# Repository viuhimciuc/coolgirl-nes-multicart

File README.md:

# 🎮 COOLGIRL - Ultimate Multigame Cartridge for Nintendo Entertainment System

The goal of this project is to create a Nintendo Entertainment System (NES) cartridge in KiCad based on the [coolgirl-famicom-multicart](https://github.com/ClusterM/coolgirl-famicom-multicart) project. This hardware design remains functionally identical to ClusterM's original project and can support up to ~700 games across various mappers.

### 🛠️ Architecture Overview
* **🧠 CPLD Core**: Uses the EPM1270T144 chip to emulate various mappers.
* **💾 Memory Layout**: PRG and CHR data share a single flash memory chip.
* **⚡ Boot Sequence**: The bootloader copies CHR data from Flash to CHR-RAM before game launch.
* **⚙️ Configuration**: Registers manage PRG offsets, bank modes, and mapper IDs.
* **🔒 Security**: Features a dedicated write-protection lock bit to secure settings after configuration.

## 📋 Full Characteristics
* **PRG ROM**: Up to 128 MiB
* **CHR RAM**: Up to 512 KiB
* **PRG RAM**: 32 KiB, non-volatile (FRAM) (optional)

---

## 🚀 How to Build

### 🔌 Hardware

#### 📄 Bill of Materials
* 🛒 [BoM](Coolgirl-NES_Rev6.x/production/bom.csv)

#### 🗺️ Schematic

* The [kicad_sch](Coolgirl-NES_Rev6.x/Coolgirl-NES_Rev6.x.kicad_sch) file can be opened using [KiCad](https://kicad.org).
 
#### 🎛️ PCB Design
The board is designed for ordering on [jlcpcb.com](https://jlcpcb.com).

| 🟢 3D Render (Top) | 🔵 3D Render (Bottom) |
| :---: | :---: |
|  |  |

* **Layers**: 2
* **PCB Thickness**: 1.2mm
* **Edge Connectors**: Gold fingers are highly recommended

* 📂 Layout source: [kicad_pcb](Coolgirl-NES_Rev6.x/Coolgirl-NES_Rev6.x.kicad_pcb) can be opened using [KiCad](https://kicad.org).
* 📦 Production files: Generated gerbers are located in the [Coolgirl-NES_Rev6.x/production](Coolgirl-NES_Rev6.x/production) directory.

### 💾 Firmware
All firmware and register descriptions are sourced from the [coolgirl-famicom-multicart](https://github.com/ClusterM/coolgirl-famicom-multicart/tree/master) project, corresponding to the board revision.

EPM1270T144 CPLD firmware can be compiled using the [Quartus Prime Lite 21.1](https://www.altera.com/downloads/fpga-development-tools/quartus-prime-lite-edition-design-software-version-21-1-windows). Open [CoolGirl.qpf](https://github.com/ClusterM/coolgirl-famicom-multicart/blob/master/CoolGirl_rev6.x/CoolGirl.qpf) to configure and compile project.

All mappers can't fit into the CPLD at once, so you need to select required mappers in [config file](https://github.com/ClusterM/coolgirl-famicom-multicart/blob/master/CoolGirl_config.vh), so they can fit into 1270 macrocells. Also, you can set `RESET_COMBINATION` parameter to specify software reset button combination, it works on original consoles and some famiclones. Default combination is `8'b11010010` (Left+Start+A+B). Set it to 0 to disable and free some macrocells.

There are JTAG pads on the cartridge board to connect programmer (USB Blaster).

### 💿 ROM Preparing
You can use my [COOLGIRL Multirom Builder based on ca65](https://github.com/viuhimciuc/coolgirl-multirom-builder-ca65)

and also use from [COOLGIRL Multirom Builder](https://github.com/ClusterM/coolgirl-multirom-builder)

to combine multiple ROMs into one with menu and loader. ROM can be written to assembled cartridge using [Famicom/NES Dumper/Writer](https://github.com/ClusterM/famicom-dumper-writer). Non-soldered flash memory chip can be written using programmer.

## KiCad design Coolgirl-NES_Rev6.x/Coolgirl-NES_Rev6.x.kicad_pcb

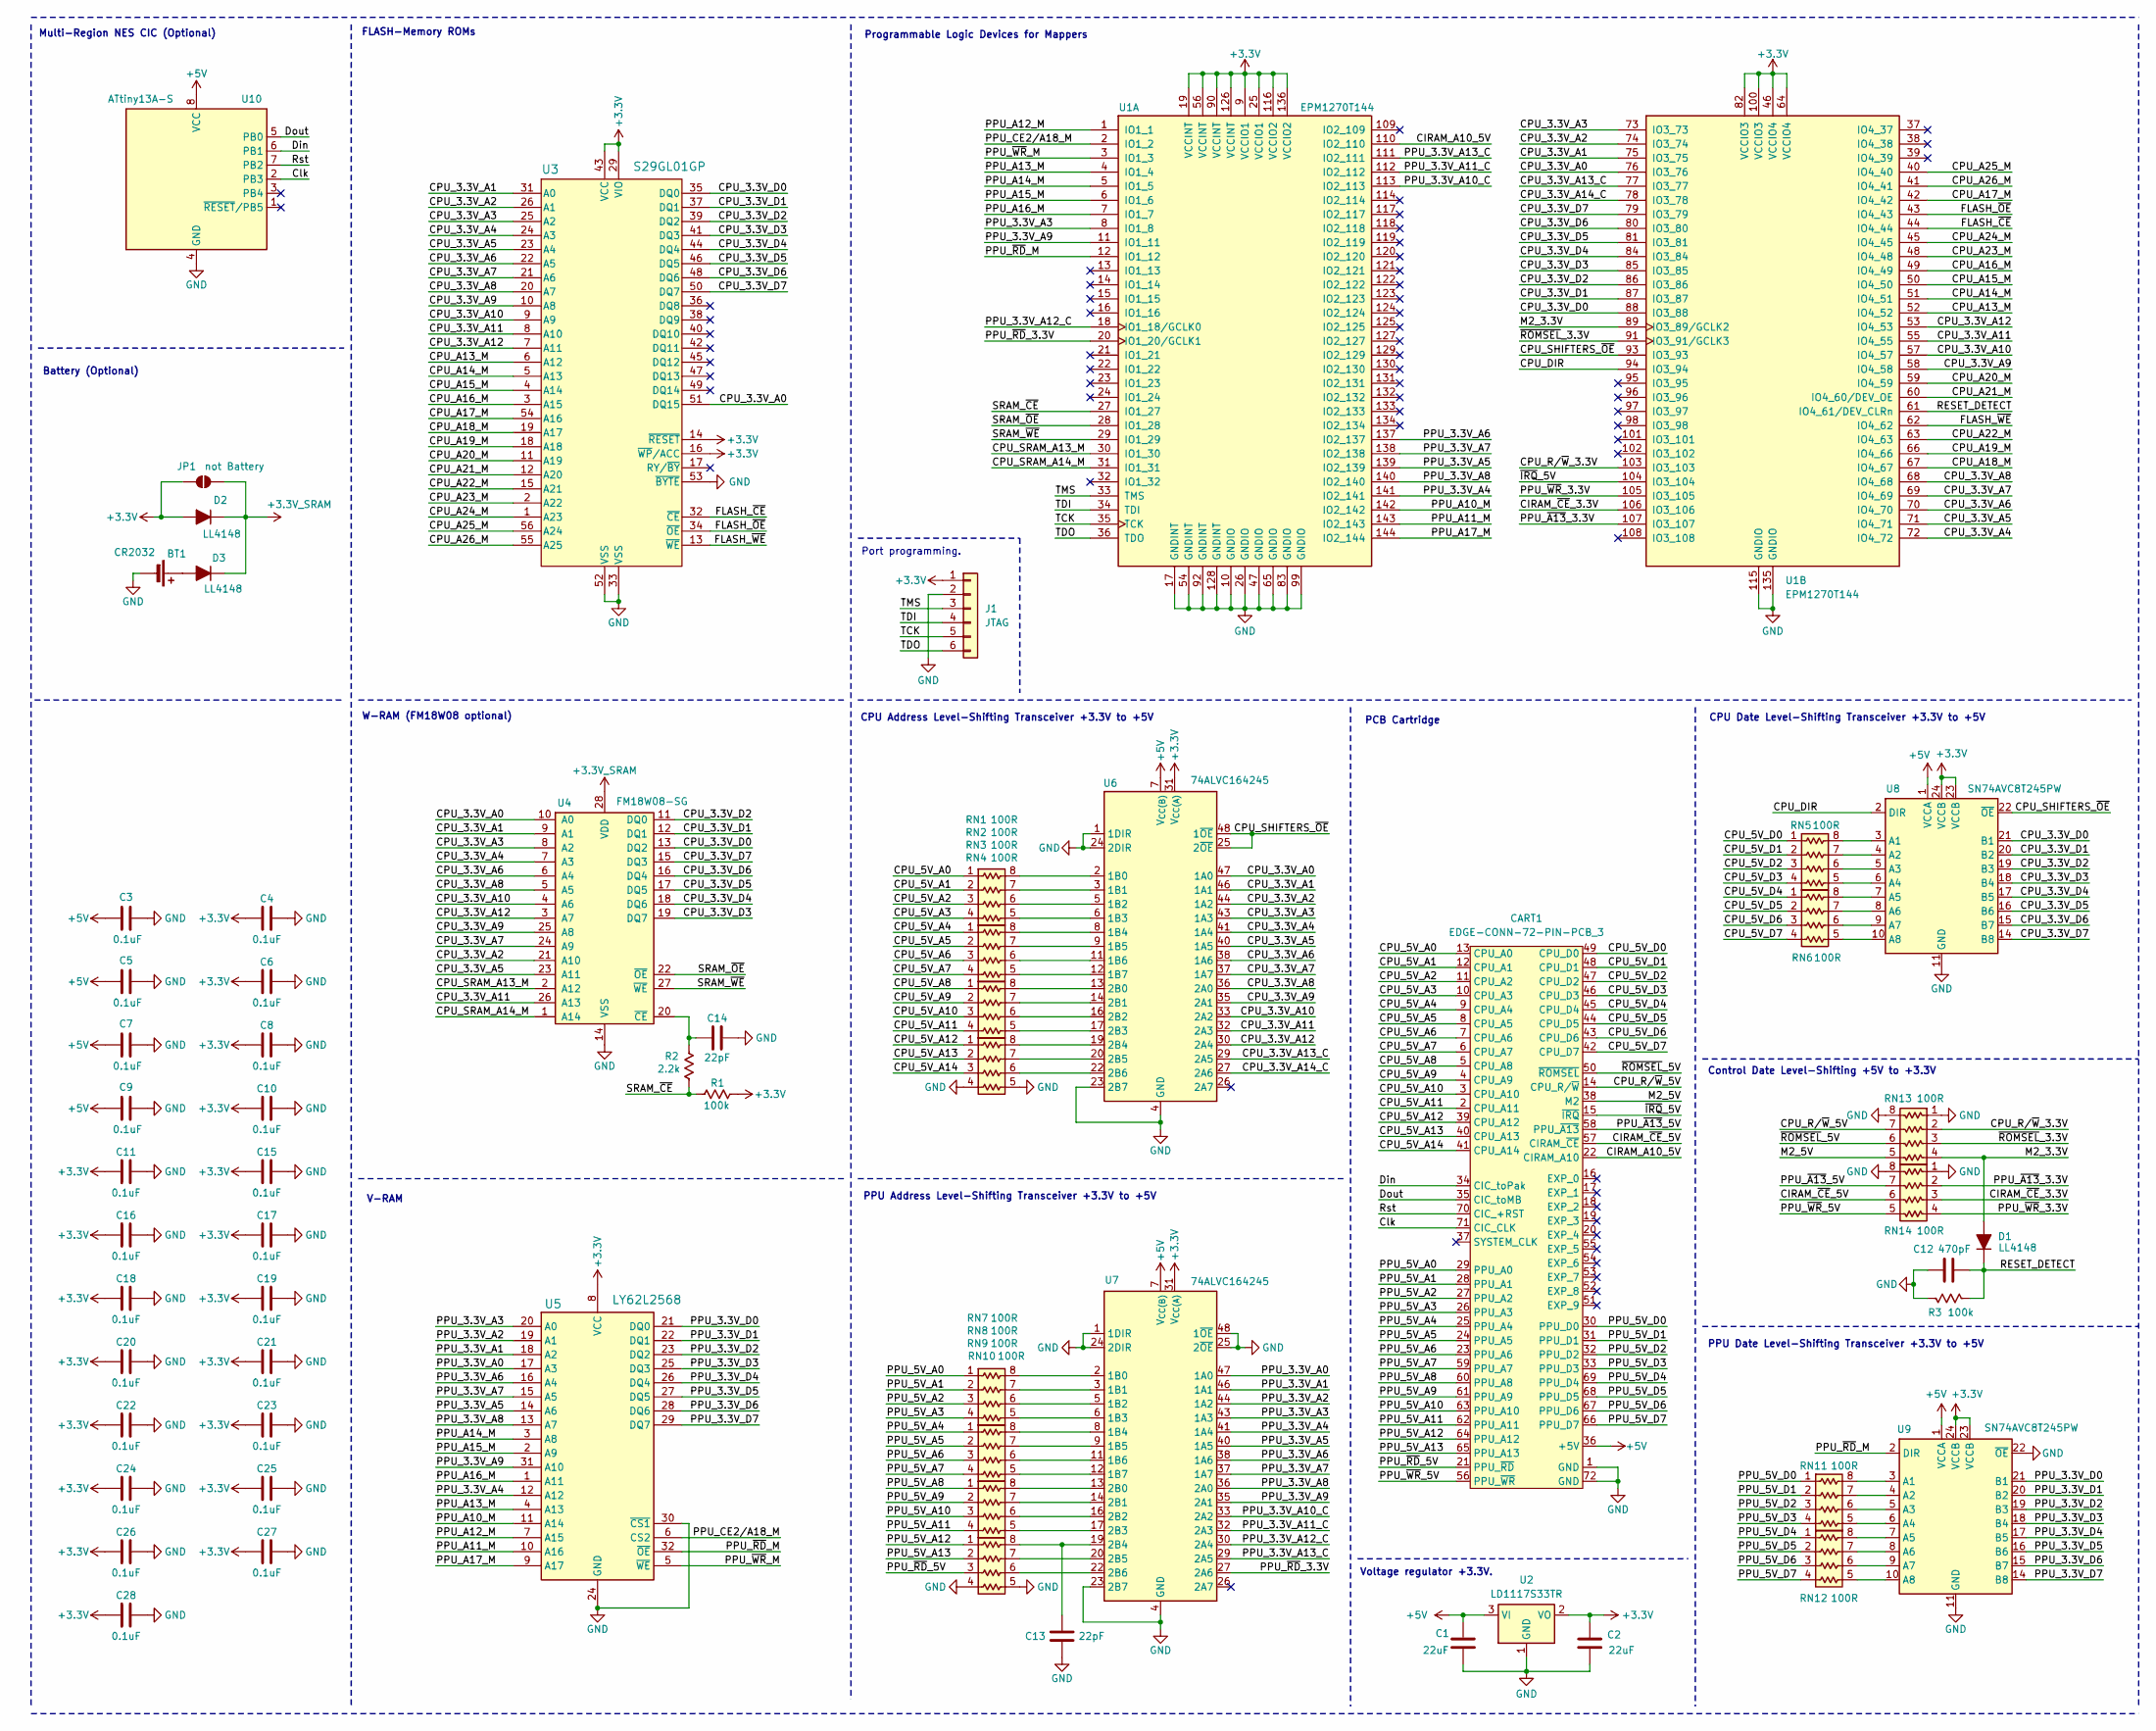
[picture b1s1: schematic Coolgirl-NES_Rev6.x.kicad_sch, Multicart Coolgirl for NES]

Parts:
BT1: CR2032; BatteryHolder_Keystone_1060_1x2032
C1, C2: 22uF; C_0603_1608Metric_Pad1.08x0.95mm_HandSolder
C3, C4, C5, C6, C7, C8, C9, C10, C11, C15, C16, C17, C18, C19, C20, C21, C22, C23, C24, C25, C26, C27, C28: 0.1uF; C_0402_1005Metric_Pad0.74x0.62mm_HandSolder
C12: 470pF; C_0402_1005Metric_Pad0.74x0.62mm_HandSolder
C13, C14: 22pF; C_0402_1005Metric_Pad0.74x0.62mm_HandSolder
CART1: EDGE-CONN-72-PIN-PCB_3; PCB_3-CART-72-2.50-CONN
D1, D2, D3: LL4148; D_MiniMELF
J1: JTAG; PinHeader_1x06_P2.54mm_Horizontal
JP1: not Battery; SolderJumper-2_P1.3mm_Open_RoundedPad1.0x1.5mm
R1, R3: 100k; R_0402_1005Metric_Pad0.72x0.64mm_HandSolder
R2: 2.2k; R_0402_1005Metric_Pad0.72x0.64mm_HandSolder
RN1, RN2, RN3, RN4, RN5, RN6, RN7, RN8, RN9, RN10, RN11, RN12, RN13, RN14: 100R; R_Array_Concave_4x0402
U1: EPM1270T144; LQFP-144_20x20mm_P0.5mm
U2: LD1117S33TR; SOT-223-3_TabPin2
U3: S29GL01GP; TSOP-I-56_18.4x14mm_P0.5mm
U4: FM18W08-SG; SOIC-28W_7.5x17.9mm_P1.27mm
U5: LY62L2568; TSOP-I-32_11.8x8mm_P0.5mm
U6, U7: 74ALVC164245; TSSOP-48_6.1x12.5mm_P0.5mm
U8, U9: SN74AVC8T245PW; TSSOP-24_4.4x7.8mm_P0.65mm
U10: ATtiny13A-S; SOIC-8_5.3x5.3mm_P1.27mm

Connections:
+3.3V: C2.1, C4.1, C6.1, C8.1, C10.1, C11.1, C15.1, C16.1, C17.1, C18.1, C19.1, C20.1, C21.1, C22.1, C23.1, C24.1, C25.1, C26.1, C27.1, C28.1, D2.2 (A), J1.1, JP1.1 (A), R1.1, U1.9 (VCCIO1), U1.19 (VCCINT), U1.25 (VCCIO1), U1.46 (VCCIO4), U1.56 (VCCINT), U1.64 (VCCIO4), U1.82 (VCCIO3), U1.90 (VCCINT), U1.100 (VCCIO3), U1.116 (VCCIO2), U1.126 (VCCINT), U1.136 (VCCIO2), U2.2 (VO), U3.14 (~RESET), U3.16 (~WP/ACC), U3.29 (VIO), U3.43 (VCC), U5.8 (VCC), U6.31 (V_{CC(A)}), U6.42 (V_{CC(A)}), U7.31 (V_{CC(A)}), U7.42 (V_{CC(A)}), U8.23 (VCCB), U8.24 (VCCB), U9.23 (VCCB), U9.24 (VCCB)
+3.3V_SRAM: D2.1 (K), D3.1 (K), JP1.2 (B), U4.28 (VDD)
+5V: C1.1, C3.1, C5.1, C7.1, C9.1, CART1.36 (+5V), U2.3 (VI), U6.7 (V_{CC(B)}), U6.18 (V_{CC(B)}), U7.7 (V_{CC(B)}), U7.18 (V_{CC(B)}), U8.1 (VCCA), U9.1 (VCCA), U10.8 (VCC)
/CIRAM_A10_5V: CART1.22 (CIRAM_A10), U1.110 (IO2_110)
/CIRAM_~CE_3.3V: RN14.3 (R3.1), U1.106 (IO3_106)
/CIRAM_~CE_5V: CART1.57 (CIRAM_~CE), RN14.6 (R3.2)
/CPU_3.3V_A0: U1.76 (IO3_76), U3.51 (DQ15), U4.10 (A0), U6.47 (1A0)
/CPU_3.3V_A1: U1.75 (IO3_75), U3.31 (A0), U4.9 (A1), U6.46 (1A1)
/CPU_3.3V_A2: U1.74 (IO3_74), U3.26 (A1), U4.21 (A10), U6.44 (1A2)
/CPU_3.3V_A3: U1.73 (IO3_73), U3.25 (A2), U4.8 (A2), U6.43 (1A3)
/CPU_3.3V_A4: U1.72 (IO4_72), U3.24 (A3), U4.7 (A3), U6.41 (1A4)
/CPU_3.3V_A5: U1.71 (IO4_71), U3.23 (A4), U4.23 (A11), U6.40 (1A5)
/CPU_3.3V_A6: U1.70 (IO4_70), U3.22 (A5), U4.6 (A4), U6.38 (1A6)
/CPU_3.3V_A7: U1.69 (IO4_69), U3.21 (A6), U4.24 (A9), U6.37 (1A7)
/CPU_3.3V_A8: U1.68 (IO4_68), U3.20 (A7), U4.5 (A5), U6.36 (2A0)
/CPU_3.3V_A9: U1.58 (IO4_58), U3.10 (A8), U4.25 (A8), U6.35 (2A1)
/CPU_3.3V_A10: U1.57 (IO4_57), U3.9 (A9), U4.4 (A6), U6.33 (2A2)
/CPU_3.3V_A11: U1.55 (IO4_55), U3.8 (A10), U4.26 (A13), U6.32 (2A3)
/CPU_3.3V_A12: U1.53 (IO4_53), U3.7 (A11), U4.3 (A7), U6.30 (2A4)
/CPU_3.3V_A13_C: U1.77 (IO3_77), U6.29 (2A5)
/CPU_3.3V_A14_C: U1.78 (IO3_78), U6.27 (2A6)
/CPU_3.3V_D0: U1.88 (IO3_88), U3.35 (DQ0), U4.13 (DQ2), U8.21 (B1)
/CPU_3.3V_D1: U1.87 (IO3_87), U3.37 (DQ1), U4.12 (DQ1), U8.20 (B2)
/CPU_3.3V_D2: U1.86 (IO3_86), U3.39 (DQ2), U4.11 (DQ0), U8.19 (B3)
/CPU_3.3V_D3: U1.85 (IO3_85), U3.41 (DQ3), U4.19 (DQ7), U8.18 (B4)
/CPU_3.3V_D4: U1.84 (IO3_84), U3.44 (DQ4), U4.18 (DQ6), U8.17 (B5)
/CPU_3.3V_D5: U1.81 (IO3_81), U3.46 (DQ5), U4.17 (DQ5), U8.16 (B6)
/CPU_3.3V_D6: U1.80 (IO3_80), U3.48 (DQ6), U4.16 (DQ4), U8.15 (B7)
/CPU_3.3V_D7: U1.79 (IO3_79), U3.50 (DQ7), U4.15 (DQ3), U8.14 (B8)
/CPU_5V_A0: CART1.13 (CPU_A0), RN1.1 (R1.1)
/CPU_5V_A1: CART1.12 (CPU_A1), RN1.2 (R2.1)
/CPU_5V_A2: CART1.11 (CPU_A2), RN1.3 (R3.1)
/CPU_5V_A3: CART1.10 (CPU_A3), RN1.4 (R4.1)
/CPU_5V_A4: CART1.9 (CPU_A4), RN2.1 (R1.1)
/CPU_5V_A5: CART1.8 (CPU_A5), RN2.2 (R2.1)
/CPU_5V_A6: CART1.7 (CPU_A6), RN2.3 (R3.1)
/CPU_5V_A7: CART1.6 (CPU_A7), RN2.4 (R4.1)
/CPU_5V_A8: CART1.5 (CPU_A8), RN3.1 (R1.1)
/CPU_5V_A9: CART1.4 (CPU_A9), RN3.2 (R2.1)
/CPU_5V_A10: CART1.3 (CPU_A10), RN3.3 (R3.1)
/CPU_5V_A11: CART1.2 (CPU_A11), RN3.4 (R4.1)
/CPU_5V_A12: CART1.39 (CPU_A12), RN4.1 (R1.1)
/CPU_5V_A13: CART1.40 (CPU_A13), RN4.2 (R2.1)
/CPU_5V_A14: CART1.41 (CPU_A14), RN4.3 (R3.1)
/CPU_5V_D0: CART1.49 (CPU_D0), RN5.1 (R1.1)
/CPU_5V_D1: CART1.48 (CPU_D1), RN5.2 (R2.1)
/CPU_5V_D2: CART1.47 (CPU_D2), RN5.3 (R3.1)
/CPU_5V_D3: CART1.46 (CPU_D3), RN5.4 (R4.1)
/CPU_5V_D4: CART1.45 (CPU_D4), RN6.1 (R1.1)
/CPU_5V_D5: CART1.44 (CPU_D5), RN6.2 (R2.1)
/CPU_5V_D6: CART1.43 (CPU_D6), RN6.3 (R3.1)
/CPU_5V_D7: CART1.42 (CPU_D7), RN6.4 (R4.1)
/CPU_A13_M: U1.52 (IO4_52), U3.6 (A12)
/CPU_A14_M: U1.51 (IO4_51), U3.5 (A13)
/CPU_A15_M: U1.50 (IO4_50), U3.4 (A14)
/CPU_A16_M: U1.49 (IO4_49), U3.3 (A15)
/CPU_A17_M: U1.42 (IO4_42), U3.54 (A16)
/CPU_A18_M: U1.67 (IO4_67), U3.19 (A17)
/CPU_A19_M: U1.66 (IO4_66), U3.18 (A18)
/CPU_A20_M: U1.59 (IO4_59), U3.11 (A19)
/CPU_A21_M: U1.60 (IO4_60/DEV_OE), U3.12 (A20)
/CPU_A22_M: U1.63 (IO4_63), U3.15 (A21)
/CPU_A23_M: U1.48 (IO4_48), U3.2 (A22)
/CPU_A24_M: U1.45 (IO4_45), U3.1 (A23)
/CPU_A25_M: U1.40 (IO4_40), U3.56 (A24)
/CPU_A26_M: U1.41 (IO4_41), U3.55 (A25)
/CPU_DIR: U1.94 (IO3_94), U8.2 (DIR)
/CPU_R/~W_3.3V: RN13.2 (R2.1), U1.103 (IO3_103)
/CPU_R/~W_5V: CART1.14 (CPU_R/~W), RN13.7 (R2.2)
/CPU_SHIFTERS_~OE: U1.93 (IO3_93), U6.25 (2~OE), U6.48 (1~OE), U8.22 (~OE)
/CPU_SRAM_A13_M: U1.30 (IO1_30), U4.2 (A12)
/CPU_SRAM_A14_M: U1.31 (IO1_31), U4.1 (A14)
/Clk: CART1.71 (CIC_CLK), U10.2 (PB3)
/Din: CART1.34 (CIC_toPak), U10.6 (PB1)
/Dout: CART1.35 (CIC_toMB), U10.5 (PB0)
/FLASH_~CE: U1.44 (IO4_44), U3.32 (~CE)
/FLASH_~OE: U1.43 (IO4_43), U3.34 (~OE)
/FLASH_~WE: U1.62 (IO4_62), U3.13 (~WE)
/M2_3.3V: D1.2 (A), RN13.4 (R4.1), U1.89 (IO3_89/GCLK2)
/M2_5V: CART1.38 (M2), RN13.5 (R4.2)
/PPU_3.3V_A0: U5.17 (A3), U7.47 (1A0)
/PPU_3.3V_A1: U5.18 (A2), U7.46 (1A1)
/PPU_3.3V_A2: U5.19 (A1), U7.44 (1A2)
/PPU_3.3V_A3: U1.8 (IO1_8), U5.20 (A0), U7.43 (1A3)
/PPU_3.3V_A4: U1.141 (IO2_141), U5.12 (A12), U7.41 (1A4)
/PPU_3.3V_A5: U1.139 (IO2_139), U5.14 (A6), U7.40 (1A5)
/PPU_3.3V_A6: U1.137 (IO2_137), U5.16 (A4), U7.38 (1A6)
/PPU_3.3V_A7: U1.138 (IO2_138), U5.15 (A5), U7.37 (1A7)
/PPU_3.3V_A8: U1.140 (IO2_140), U5.13 (A7), U7.36 (2A0)
/PPU_3.3V_A9: U1.11 (IO1_11), U5.31 (A10), U7.35 (2A1)
/PPU_3.3V_A10_C: U1.113 (IO2_113), U7.33 (2A2)
/PPU_3.3V_A11_C: U1.112 (IO2_112), U7.32 (2A3)
/PPU_3.3V_A12_C: U1.18 (IO1_18/GCLK0), U7.30 (2A4)
/PPU_3.3V_A13_C: U1.111 (IO2_111), U7.29 (2A5)
/PPU_3.3V_D0: U5.21 (DQ0), U9.21 (B1)
/PPU_3.3V_D1: U5.22 (DQ1), U9.20 (B2)
/PPU_3.3V_D2: U5.23 (DQ2), U9.19 (B3)
/PPU_3.3V_D3: U5.25 (DQ3), U9.18 (B4)
/PPU_3.3V_D4: U5.26 (DQ4), U9.17 (B5)
/PPU_3.3V_D5: U5.27 (DQ5), U9.16 (B6)
/PPU_3.3V_D6: U5.28 (DQ6), U9.15 (B7)
/PPU_3.3V_D7: U5.29 (DQ7), U9.14 (B8)
/PPU_5V_A0: CART1.29 (PPU_A0), RN7.1 (R1.1)
/PPU_5V_A1: CART1.28 (PPU_A1), RN7.2 (R2.1)
/PPU_5V_A2: CART1.27 (PPU_A2), RN7.3 (R3.1)
/PPU_5V_A3: CART1.26 (PPU_A3), RN7.4 (R4.1)
/PPU_5V_A4: CART1.25 (PPU_A4), RN8.1 (R1.1)
/PPU_5V_A5: CART1.24 (PPU_A5), RN8.2 (R2.1)
/PPU_5V_A6: CART1.23 (PPU_A6), RN8.3 (R3.1)
/PPU_5V_A7: CART1.59 (PPU_A7), RN8.4 (R4.1)
/PPU_5V_A8: CART1.60 (PPU_A8), RN9.1 (R1.1)
/PPU_5V_A9: CART1.61 (PPU_A9), RN9.2 (R2.1)
/PPU_5V_A10: CART1.63 (PPU_A10), RN9.3 (R3.1)
/PPU_5V_A11: CART1.62 (PPU_A11), RN9.4 (R4.1)
/PPU_5V_A12: CART1.64 (PPU_A12), RN10.1 (R1.1)
/PPU_5V_A13: CART1.65 (PPU_A13), RN10.2 (R2.1)
/PPU_5V_D0: CART1.30 (PPU_D0), RN11.1 (R1.1)
/PPU_5V_D1: CART1.31 (PPU_D1), RN11.2 (R2.1)
/PPU_5V_D2: CART1.32 (PPU_D2), RN11.3 (R3.1)
/PPU_5V_D3: CART1.33 (PPU_D3), RN11.4 (R4.1)
/PPU_5V_D4: CART1.69 (PPU_D4), RN12.1 (R1.1)
/PPU_5V_D5: CART1.68 (PPU_D5), RN12.2 (R2.1)
/PPU_5V_D6: CART1.67 (PPU_D6), RN12.3 (R3.1)
/PPU_5V_D7: CART1.66 (PPU_D7), RN12.4 (R4.1)
/PPU_A10_M: U1.142 (IO2_142), U5.11 (A14)
/PPU_A11_M: U1.143 (IO2_143), U5.10 (A16)
/PPU_A12_M: U1.1 (IO1_1), U5.7 (A15)
/PPU_A13_M: U1.4 (IO1_4), U5.4 (A13)
/PPU_A14_M: U1.5 (IO1_5), U5.3 (A8)
/PPU_A15_M: U1.6 (IO1_6), U5.2 (A9)
/PPU_A16_M: U1.7 (IO1_7), U5.1 (A11)
/PPU_A17_M: U1.144 (IO2_144), U5.9 (A17)
/PPU_CE2/A18_M: U1.2 (IO1_2), U5.6 (CS2)
/PPU_~A13_3.3V: RN14.2 (R2.1), U1.107 (IO3_107)
/PPU_~A13_5V: CART1.58 (PPU_~A13), RN14.7 (R2.2)
/PPU_~RD_3.3V: U1.20 (IO1_20/GCLK1), U7.27 (2A6)
/PPU_~RD_5V: CART1.21 (PPU_~RD), RN10.3 (R3.1)
/PPU_~RD_M: U1.12 (IO1_12), U5.32 (~OE), U9.2 (DIR)
/PPU_~WR_3.3V: RN14.4 (R4.1), U1.105 (IO3_105)
/PPU_~WR_5V: CART1.56 (PPU_~WR), RN14.5 (R4.2)
/PPU_~WR_M: U1.3 (IO1_3), U5.5 (~WE)
/RESET_DETECT: C12.2, D1.1 (K), R3.1, U1.61 (IO4_61/DEV_CLRn)
/Rst: CART1.70 (CIC_+RST), U10.7 (PB2)
/SRAM_~CE: R1.2, R2.1, U1.27 (IO1_27)
/SRAM_~OE: U1.28 (IO1_28), U4.22 (~OE)
/SRAM_~WE: U1.29 (IO1_29), U4.27 (~WE)
/TCK: J1.5, U1.35 (TCK)
/TDI: J1.4, U1.34 (TDI)
/TDO: J1.6, U1.36 (TDO)
/TMS: J1.3, U1.33 (TMS)
/~IRQ_5V: CART1.15 (~IRQ), U1.104 (IO3_104)
/~ROMSEL_3.3V: RN13.3 (R3.1), U1.91 (IO3_91/GCLK3)
/~ROMSEL_5V: CART1.50 (~ROMSEL), RN13.6 (R3.2)
GND: BT1.2 (-), C1.2, C2.2, C3.2, C4.2, C5.2, C6.2, C7.2, C8.2, C9.2, C10.2, C11.2, C12.1, C13.1, C14.2, C15.2, C16.2, C17.2, C18.2, C19.2, C20.2, C21.2, C22.2, C23.2, C24.2, C25.2, C26.2, C27.2, C28.2, CART1.1 (GND), CART1.72 (GND), J1.2, R3.2, RN4.4 (R4.1), RN4.5 (R4.2), RN10.4 (R4.1), RN10.5 (R4.2), RN13.1 (R1.1), RN13.8 (R1.2), RN14.1 (R1.1), RN14.8 (R1.2), U1.10 (GNDIO), U1.17 (GNDINT), U1.26 (GNDIO), U1.47 (GNDIO), U1.54 (GNDINT), U1.65 (GNDIO), U1.83 (GNDIO), U1.92 (GNDINT), U1.99 (GNDIO), U1.115 (GNDIO), U1.128 (GNDINT), U1.135 (GNDIO), U2.1 (GND), U3.33 (VSS), U3.52 (VSS), U3.53 (~BYTE), U4.14 (VSS), U5.24 (GND), U5.30 (~CS1), U6.1 (1DIR), U6.4 (GND), U6.10 (GND), U6.15 (GND), U6.21 (GND), U6.23 (2B7), U6.24 (2DIR), U6.28 (GND), U6.34 (GND), U6.39 (GND), U6.45 (GND), U7.1 (1DIR), U7.4 (GND), U7.10 (GND), U7.15 (GND), U7.21 (GND), U7.23 (2B7), U7.24 (2DIR), U7.25 (2~OE), U7.28 (GND), U7.34 (GND), U7.39 (GND), U7.45 (GND), U7.48 (1~OE), U8.11 (GND), U8.12 (GND), U8.13 (GND), U9.11 (GND), U9.12 (GND), U9.13 (GND), U9.22 (~OE), U10.4 (GND)
unnamed: BT1.1 (+), D3.2 (A)
unnamed: RN1.8 (R1.2), U6.2 (1B0)
unnamed: RN1.7 (R2.2), U6.3 (1B1)
unnamed: RN1.6 (R3.2), U6.5 (1B2)
unnamed: RN1.5 (R4.2), U6.6 (1B3)
unnamed: RN2.8 (R1.2), U6.8 (1B4)
unnamed: RN2.7 (R2.2), U6.9 (1B5)
unnamed: RN2.6 (R3.2), U6.11 (1B6)
unnamed: RN2.5 (R4.2), U6.12 (1B7)
unnamed: RN3.8 (R1.2), U6.13 (2B0)
unnamed: RN3.7 (R2.2), U6.14 (2B1)
unnamed: RN3.6 (R3.2), U6.16 (2B2)
unnamed: RN3.5 (R4.2), U6.17 (2B3)
unnamed: RN4.8 (R1.2), U6.19 (2B4)
unnamed: RN4.7 (R2.2), U6.20 (2B5)
unnamed: RN4.6 (R3.2), U6.22 (2B6)
unnamed: RN5.8 (R1.2), U8.3 (A1)
unnamed: RN5.7 (R2.2), U8.4 (A2)
unnamed: RN5.6 (R3.2), U8.5 (A3)
unnamed: RN5.5 (R4.2), U8.6 (A4)
unnamed: RN6.8 (R1.2), U8.7 (A5)
unnamed: RN6.7 (R2.2), U8.8 (A6)
unnamed: RN6.6 (R3.2), U8.9 (A7)
unnamed: RN6.5 (R4.2), U8.10 (A8)
unnamed: RN7.8 (R1.2), U7.2 (1B0)
unnamed: RN7.7 (R2.2), U7.3 (1B1)
unnamed: RN7.6 (R3.2), U7.5 (1B2)
unnamed: RN7.5 (R4.2), U7.6 (1B3)
unnamed: RN8.8 (R1.2), U7.8 (1B4)
unnamed: RN8.7 (R2.2), U7.9 (1B5)
unnamed: RN8.6 (R3.2), U7.11 (1B6)
unnamed: RN8.5 (R4.2), U7.12 (1B7)
unnamed: RN9.8 (R1.2), U7.13 (2B0)
unnamed: RN9.7 (R2.2), U7.14 (2B1)
unnamed: RN9.6 (R3.2), U7.16 (2B2)
unnamed: RN9.5 (R4.2), U7.17 (2B3)
unnamed: C13.2, RN10.8 (R1.2), U7.19 (2B4)
unnamed: RN10.7 (R2.2), U7.20 (2B5)
unnamed: RN10.6 (R3.2), U7.22 (2B6)
unnamed: RN11.8 (R1.2), U9.3 (A1)
unnamed: RN11.7 (R2.2), U9.4 (A2)
unnamed: RN11.6 (R3.2), U9.5 (A3)
unnamed: RN11.5 (R4.2), U9.6 (A4)
unnamed: RN12.8 (R1.2), U9.7 (A5)
unnamed: RN12.7 (R2.2), U9.8 (A6)
unnamed: RN12.6 (R3.2), U9.9 (A7)
unnamed: RN12.5 (R4.2), U9.10 (A8)
unnamed: C14.1, R2.2, U4.20 (~CE)

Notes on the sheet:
Battery (Optional)
Voltage regulator +3.3V.
PPU Date Level-Shifting Transceiver +3.3V to +5V
Port programming.
Control Date Level-Shifting +5V to +3.3V
CPU Address Level-Shifting Transceiver +3.3V to +5V
FLASH-Memory ROMs
PCB Cartridge
Programmable Logic Devices for Mappers
PPU Address Level-Shifting Transceiver +3.3V to +5V
Multi-Region NES CIC (Optional)
W-RAM (FM18W08 optional)
CPU Date Level-Shifting Transceiver +3.3V to +5V
V-RAM

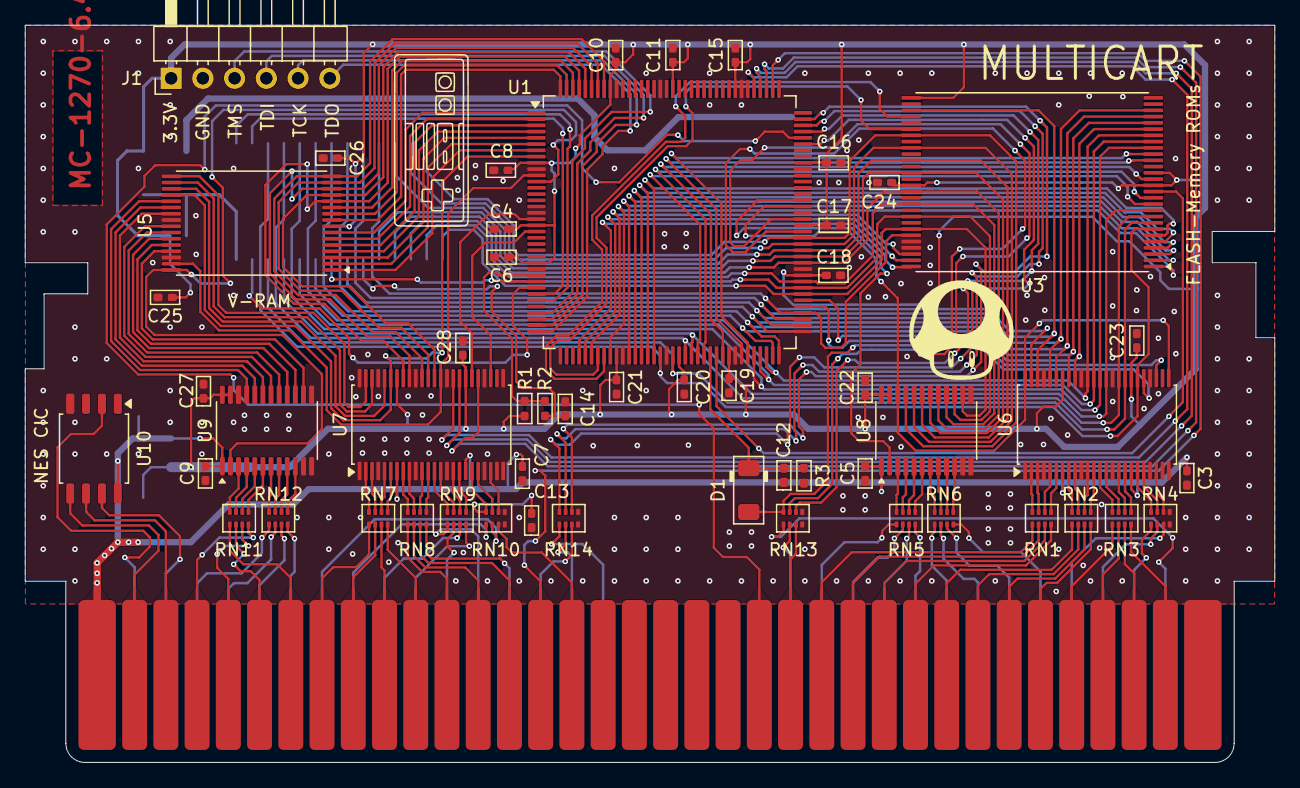
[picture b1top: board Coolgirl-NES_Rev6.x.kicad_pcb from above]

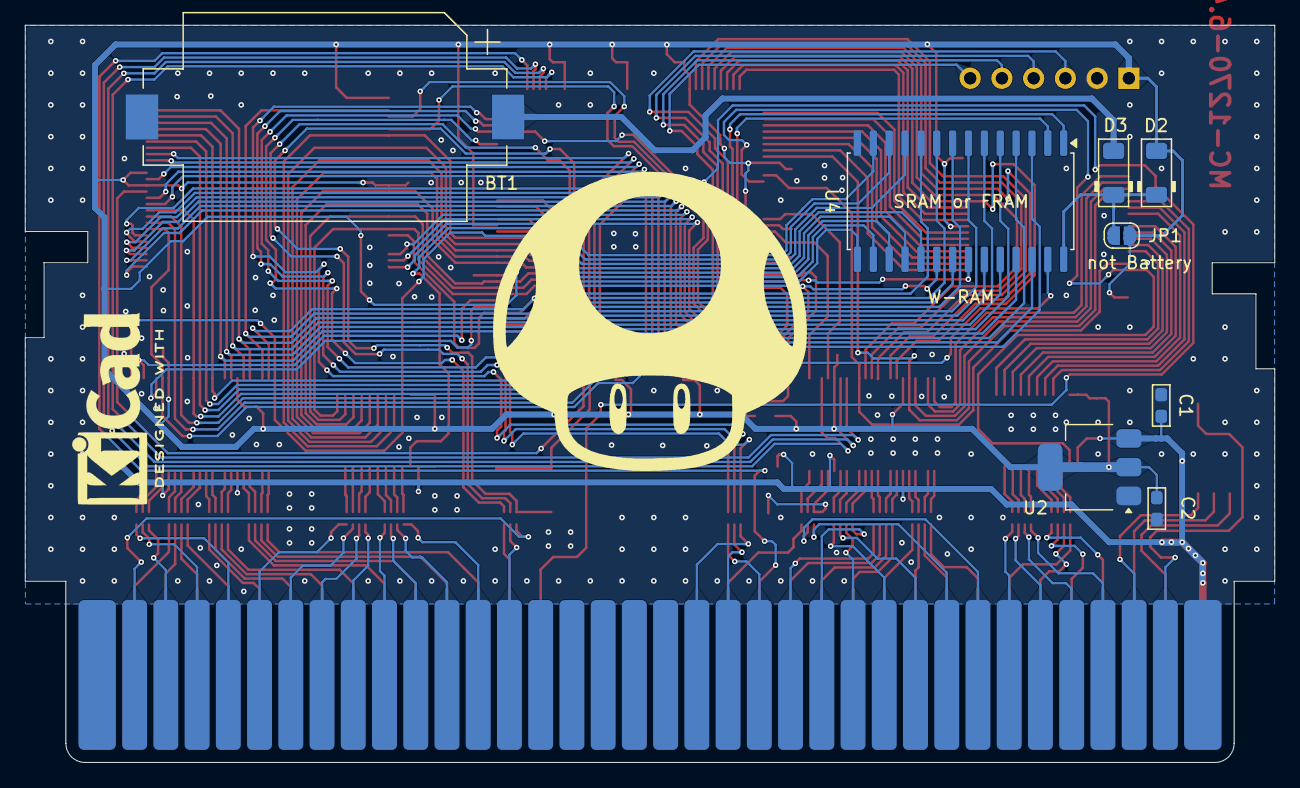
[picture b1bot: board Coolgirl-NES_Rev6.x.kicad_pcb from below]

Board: 2 copper layers, 100.0 x 59.0 mm, 62 parts (8 on the bottom side), 202 nets.

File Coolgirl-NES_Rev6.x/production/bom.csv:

Designator,Footprint,Quantity,Value,LCSC Part #
BT1,BatteryHolder_Keystone_1060_1x2032,1,CR2032,
"C1, C2",0603,2,22uF,
"C10, C11, C15, C16, C17, C18, C19, C20, C21, C22, C23, C24, C25, C26, C27, C28, C3, C4, C5, C6, C7, C8, C9",0402,23,0.1uF,
C12,0402,1,470pF,
"C13, C14",0402,2,22pF,
CART1,PCB_3-CART-72-2.50-CONN,1,EDGE-CONN-72-PIN-PCB_3,
"D1, D2, D3",D_MiniMELF,3,LL4148,
J1,PinHeader_1x06_P2.54mm_Horizontal,1,JTAG,
"R1, R3",0402,2,100k,
R2,0402,1,2.2k,
"RN1, RN10, RN11, RN12, RN13, RN14, RN2, RN3, RN4, RN5, RN6, RN7, RN8, RN9",R_Array_Concave_4x0402,14,100R,
U1,LQFP-144_20x20mm_P0.5mm,1,EPM1270T144,
U10,SOIC-8_5.3x5.3mm_P1.27mm,1,ATtiny13A-S,
U2,SOT-223-3_TabPin2,1,LD1117S33TR,
U3,TSOP-I-56_18.4x14mm_P0.5mm,1,S29GL01GP,
U4,SOIC-28W_7.5x17.9mm_P1.27mm,1,FM18W08-SG,
U5,TSOP-I-32_11.8x8mm_P0.5mm,1,LY62L2568,
"U6, U7",TSSOP-48_6.1x12.5mm_P0.5mm,2,74ALVC164245,
"U8, U9",TSSOP-24_4.4x7.8mm_P0.65mm,2,SN74AVC8T245PW,
